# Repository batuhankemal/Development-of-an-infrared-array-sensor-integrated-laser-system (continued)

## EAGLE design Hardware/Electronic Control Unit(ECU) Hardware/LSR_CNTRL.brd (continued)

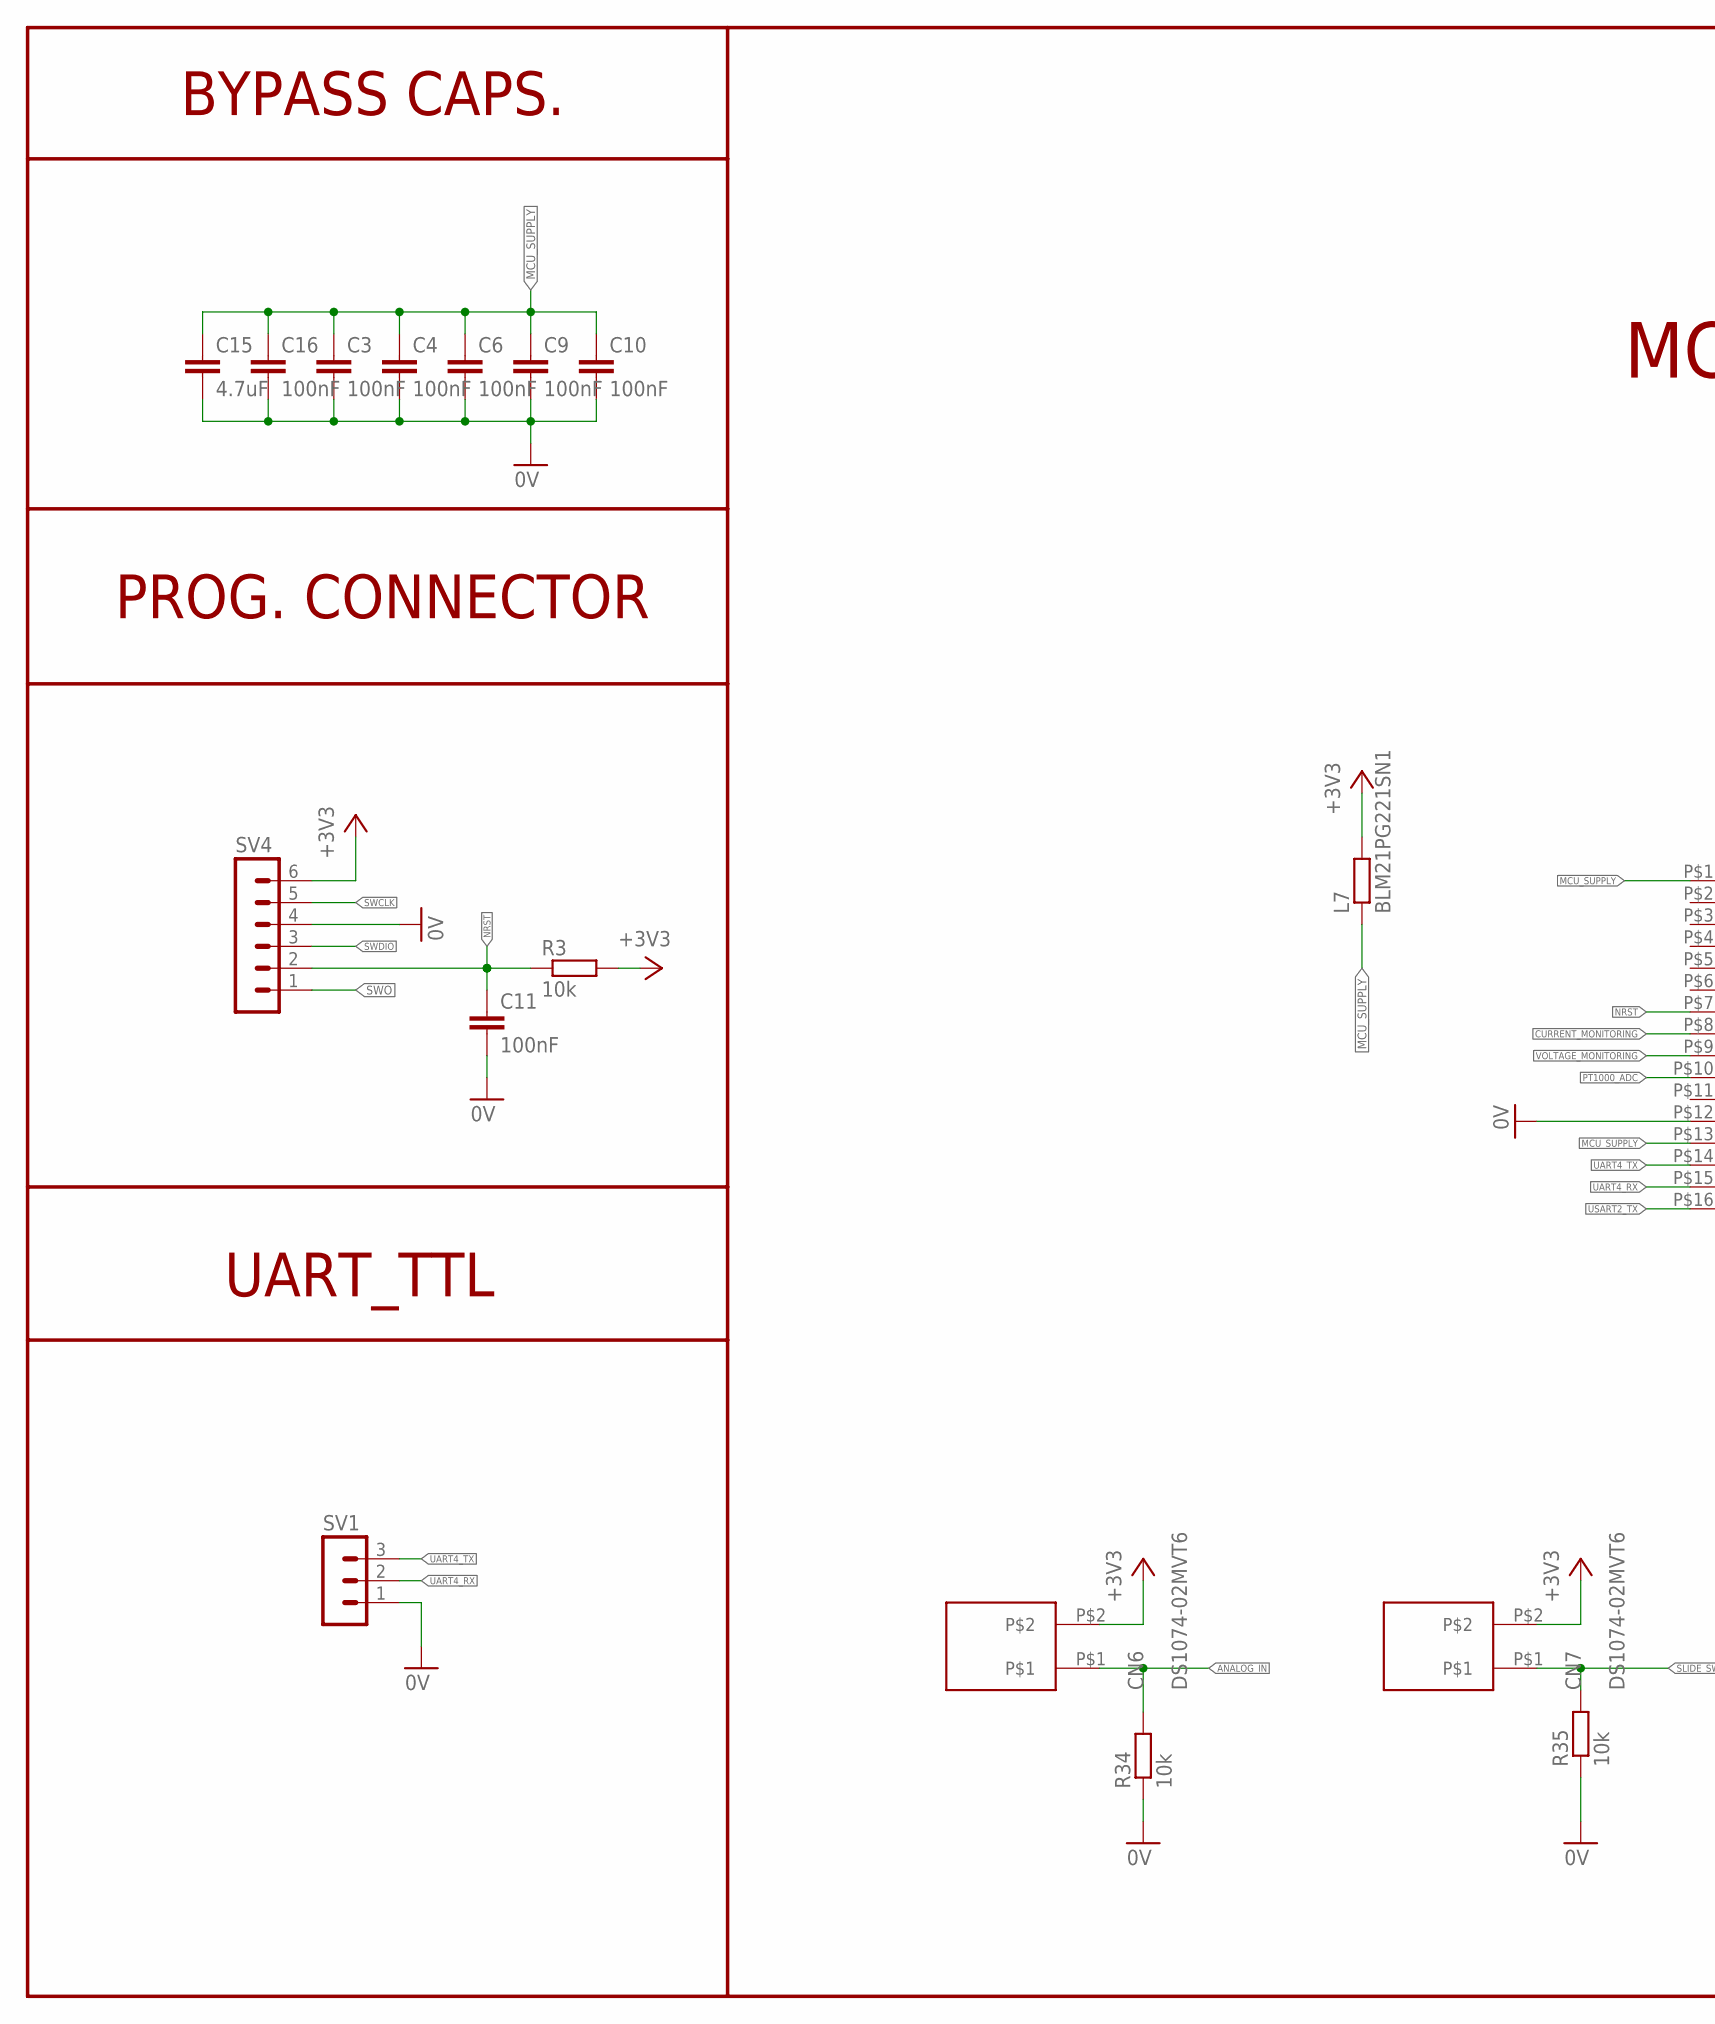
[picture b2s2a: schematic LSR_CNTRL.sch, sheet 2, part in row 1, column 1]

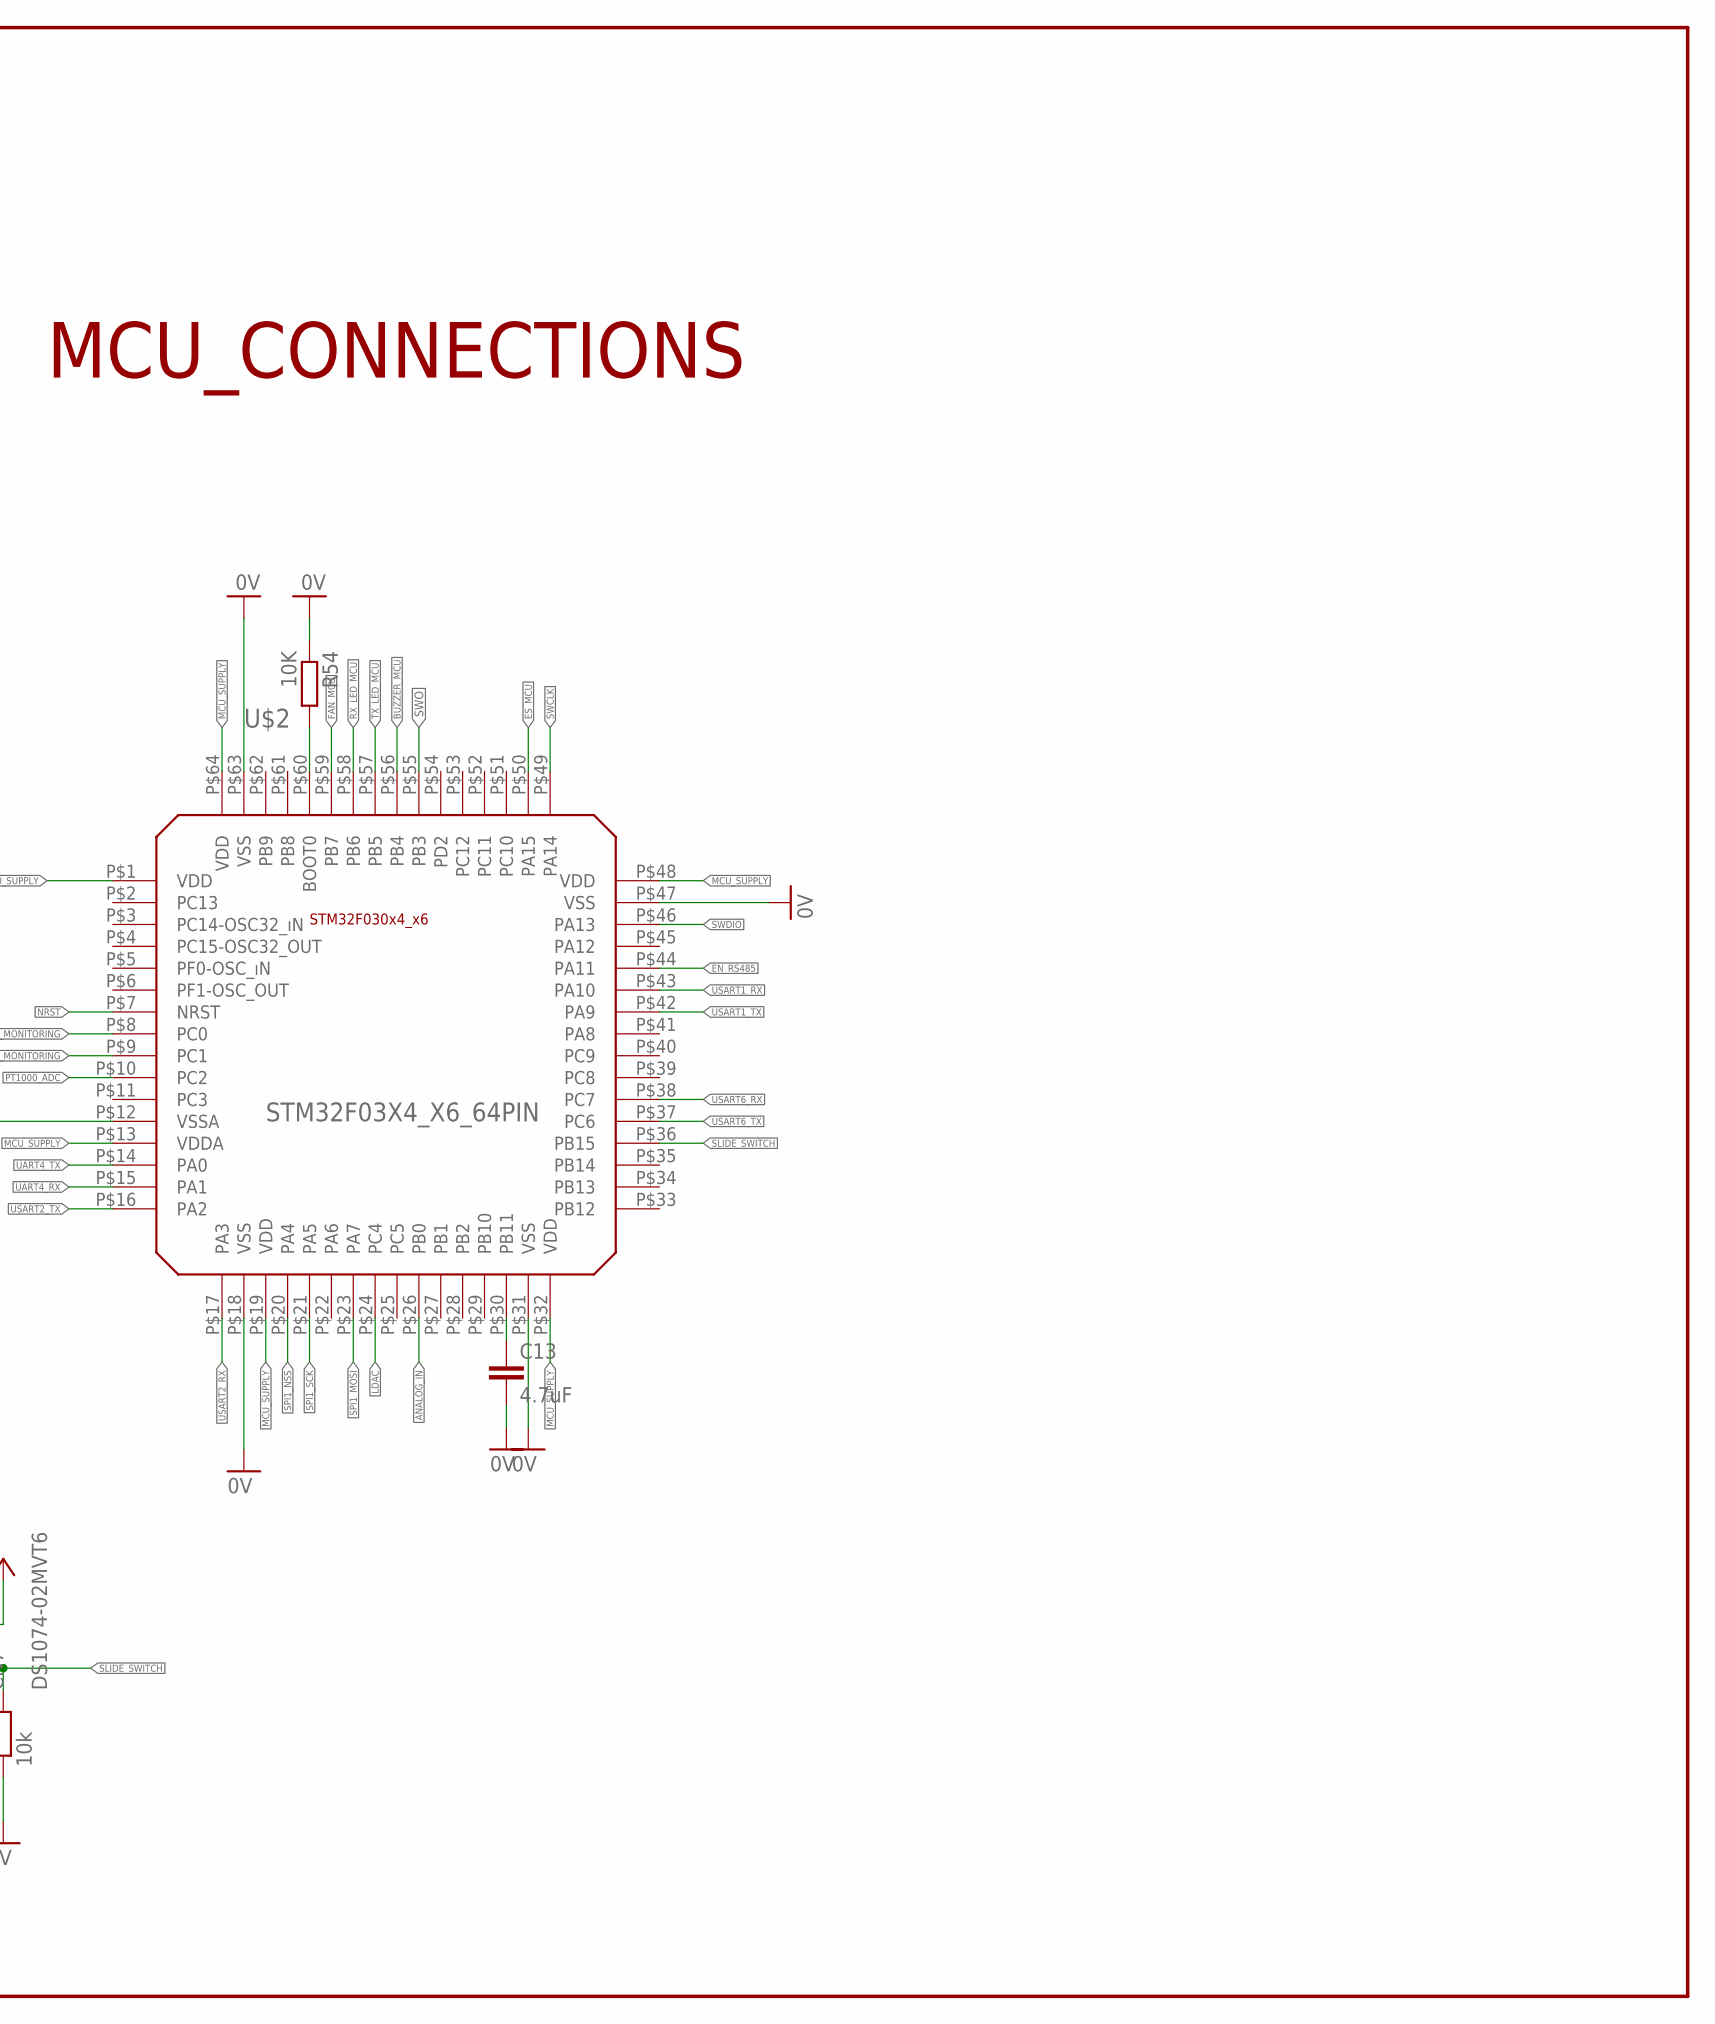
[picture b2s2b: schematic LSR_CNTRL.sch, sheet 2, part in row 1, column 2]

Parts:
C3, C4, C6, C9, C10, C11, C16: 100nF; C0603
C13, C15: 4.7uF; C0805
CN6, CN7: DS1074-02MVT6
L7: BLM21PG221SN1; R0805
R3, R34, R35: 10k; R0603
R54: 10K; R0603
SV1: MA03-1
SV4: MA06-1
U$2: STM32F03X4_X6_64PIN; LQFP64

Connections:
0V: C3.2, C4.2, C6.2, C9.2, C10.2, C11.2, C13.2, C15.2, C16.2, R34.1, R35.1, R54.1, SV1.1, SV4.4, U$2.P$12 (VSSA), U$2.P$18 (VSS), U$2.P$31 (VSS), U$2.P$47 (VSS), U$2.P$63 (VSS); also elsewhere on the board
+3V3: CN6.P$2, CN7.P$2, L7.2, R3.2, SV4.6; also elsewhere on the board
ANALOG_IN: CN6.P$1, R34.2, U$2.P$26 (PB0)
BUZZER_MCU: U$2.P$56 (PB4); also elsewhere on the board
CURRENT_MONITORING: U$2.P$8 (PC0); also elsewhere on the board
EN_RS485: U$2.P$44 (PA11); also elsewhere on the board
ES_MCU: U$2.P$50 (PA15); also elsewhere on the board
FAN_MCU: U$2.P$59 (PB7); also elsewhere on the board
LDAC: U$2.P$24 (PC4); also elsewhere on the board
MCU_SUPPLY: C3.1, C4.1, C6.1, C9.1, C10.1, C15.1, C16.1, L7.1, U$2.P$1 (VDD), U$2.P$13 (VDDA), U$2.P$19 (VDD), U$2.P$32 (VDD), U$2.P$48 (VDD), U$2.P$64 (VDD)
unnamed: C13.1, U$2.P$30 (PB11)
unnamed: R54.2, U$2.P$60 (BOOT0)
NRST: C11.1, R3.1, SV4.2, U$2.P$7 (NRST)
PT1000_ADC: U$2.P$10 (PC2); also elsewhere on the board
RX_LED_MCU: U$2.P$58 (PB6); also elsewhere on the board
SLIDE_SWITCH: CN7.P$1, R35.2, U$2.P$36 (PB15)
SPI1_MOSI: U$2.P$23 (PA7); also elsewhere on the board
SPI1_NSS: U$2.P$20 (PA4); also elsewhere on the board
SPI1_SCK: U$2.P$21 (PA5); also elsewhere on the board
SWCLK: SV4.5, U$2.P$49 (PA14)
SWDIO: SV4.3, U$2.P$46 (PA13)
SWO: SV4.1, U$2.P$55 (PB3)
TX_LED_MCU: U$2.P$57 (PB5); also elsewhere on the board
UART4_RX: SV1.2, U$2.P$15 (PA1)
UART4_TX: SV1.3, U$2.P$14 (PA0)
USART1_RX: U$2.P$43 (PA10); also elsewhere on the board
USART1_TX: U$2.P$42 (PA9); also elsewhere on the board
USART2_RX: U$2.P$17 (PA3); also elsewhere on the board
USART2_TX: U$2.P$16 (PA2); also elsewhere on the board
USART6_RX: U$2.P$38 (PC7); also elsewhere on the board
USART6_TX: U$2.P$37 (PC6); also elsewhere on the board
VOLTAGE_MONITORING: U$2.P$9 (PC1); also elsewhere on the board

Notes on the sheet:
BYPASS CAPS.
PROG. CONNECTOR
MCU_CONNECTIONS
UART_TTL

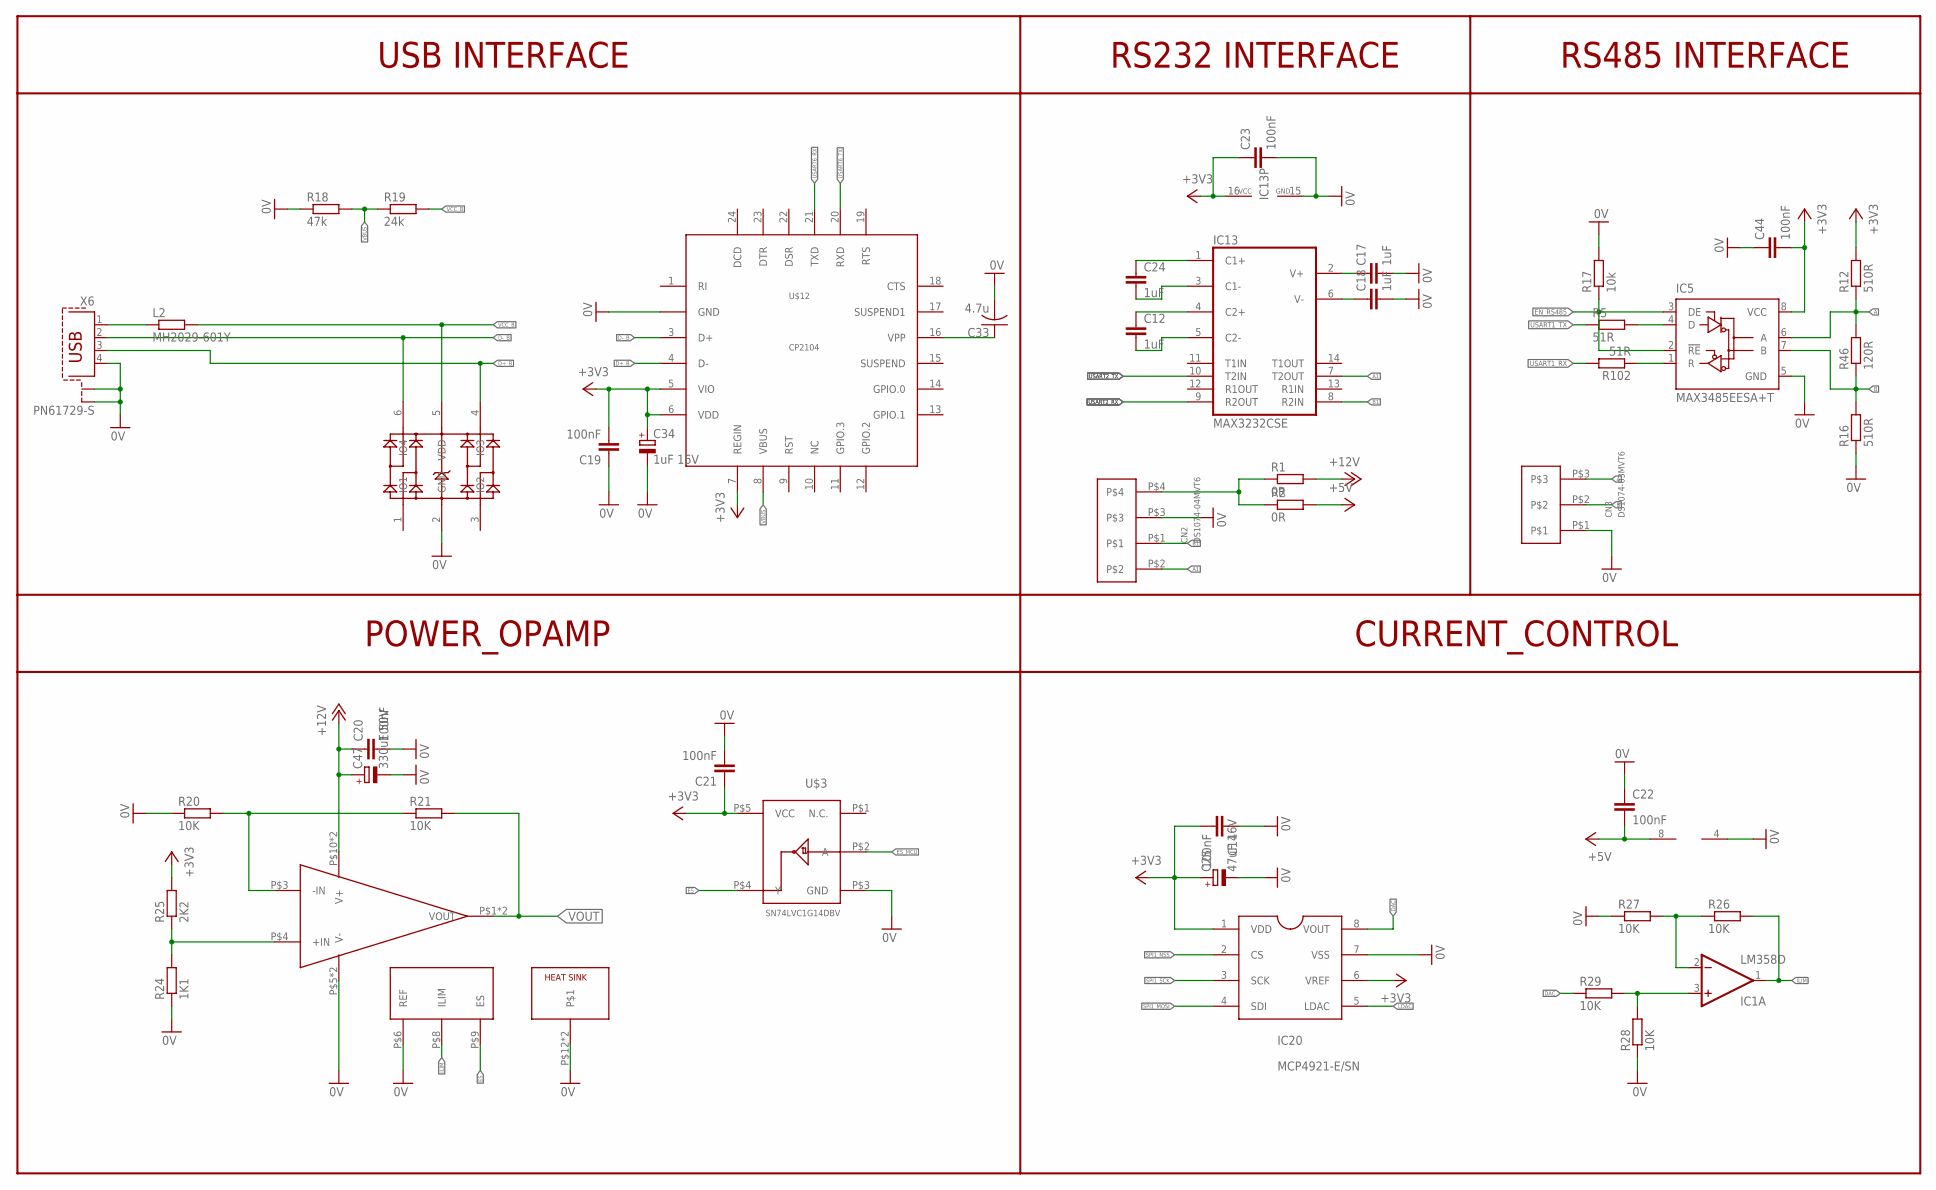
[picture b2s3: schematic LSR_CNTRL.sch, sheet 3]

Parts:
C12, C17, C18, C24: 1uF; C1206
C14, C19, C20, C21, C22, C23, C44: 100nF; C0603
C25: 47uF 16V; B/3528-21R
C33: 4.7u; C0805
C34: 1uF 16V; SMC_Z
C47: 330uF 50V; E5-10,5
CN2: DS1074-04MVT6
CN3: DS1074-03MVT6
IC1: LM358D; SO08
IC5: MAX3485EESA+T; D_R-PDSO-G8
IC13: MAX3232CSE; SO16
IC20: MCP4921-E/SN; SO-08-MCP
L2: MH2029-601Y; R0805
OPAMP1: OPA549MKVC
R1, R2: 0R; R0805
R5, R102: 51R; R0603
R12, R16: 510R; R0603
R17: 10k; R0603
R18: 47k; R0805
R19: 24k; R0805
R20, R21, R26, R27, R28, R29: 10K; R0805
R24: 1K1; R0805
R25: 2K2; R0805
R46: 120R; R0603
TVS1: 824001; SOT23-6
U$3: SN74LVC1G14DBV; SOT-23-DBV
U$12: CP2104
X6: PN61729-S

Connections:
0V: C14.1, C17.2, C18.2, C19.1, C20.2, C21.2, C22.1, C23.2, C25.-, C33.2, C34.-, C44.1, C47.-, CN2.P$3, CN3.P$1, IC1.4 (V-), IC5.5 (GND), IC13.15 (GND), IC20.7 (VSS), OPAMP1.P$5 (V-), OPAMP1.P$6 (REF), OPAMP1.P$7 (V-), OPAMP1.P$12, OPAMP1.P$13, R16.1, R17.2, R18.1, R20.1, R24.1, R27.1, R28.1, TVS1.2 (GND), U$3.P$3 (GND), U$12.2 (GND), U$12.GND1 (GND), X6.4, X6.S1, X6.S2; also elsewhere on the board
+3V3: C14.2, C19.2, C21.1, C23.1, C25.+, C34.+, C44.2, IC5.8 (VCC), IC13.16 (VCC), IC20.1 (VDD), IC20.6 (VREF), R12.2, R25.2, U$3.P$5 (VCC), U$12.5 (VIO), U$12.6 (VDD), U$12.7 (REGIN); also elsewhere on the board
+5V: C22.2, IC1.8 (V+), R2.2; also elsewhere on the board
+12V: C20.1, C47.+, OPAMP1.P$10 (V+), OPAMP1.P$11 (V+), R1.2; also elsewhere on the board
A: CN3.P$3, IC5.6 (A), R12.1, R46.2
A1: CN2.P$2, IC13.7 (T2OUT)
B: CN3.P$2, IC5.7 (B), R16.2, R46.1
B1: CN2.P$1, IC13.8 (R2IN)
D+_B: TVS1.4 (IO3), U$12.4 (D-), X6.3
D-_B: TVS1.6 (IO4), U$12.3 (D+), X6.2
DAC: IC20.8 (VOUT), R29.1
EN_RS485: IC5.2 (!RE), IC5.3 (DE), R17.1; also elsewhere on the board
ES: OPAMP1.P$9 (ES), U$3.P$4 (Y)
ES_MCU: U$3.P$2 (A); also elsewhere on the board
ILIM: IC1.1 (OUT), OPAMP1.P$8 (ILIM), R26.2
LDAC: IC20.5 (LDAC); also elsewhere on the board
unnamed: C18.1, IC13.6 (V-)
unnamed: OPAMP1.P$3 (-IN), R20.2, R21.1
unnamed: IC1.2 (-IN), R26.1, R27.2
unnamed: OPAMP1.P$4 (+IN), R24.2, R25.1
unnamed: IC1.3 (+IN), R28.2, R29.2
unnamed: IC5.4 (D), R5.2
unnamed: C33.1, U$12.16 (VPP)
unnamed: L2.1, X6.1
unnamed: C24.1, IC13.1 (C1+)
unnamed: C24.2, IC13.3 (C1-)
unnamed: IC5.1 (R), R102.1
unnamed: C12.1, IC13.4 (C2+)
unnamed: C12.2, IC13.5 (C2-)
unnamed: C17.1, IC13.2 (V+)
SPI1_MOSI: IC20.4 (SDI); also elsewhere on the board
SPI1_NSS: IC20.2 (CS); also elsewhere on the board
SPI1_SCK: IC20.3 (SCK); also elsewhere on the board
SUPPLY: CN2.P$4, R1.1, R2.1
USART1_RX: R102.2; also elsewhere on the board
USART1_TX: R5.1; also elsewhere on the board
USART2_RX: IC13.9 (R2OUT); also elsewhere on the board
USART2_TX: IC13.10 (T2IN); also elsewhere on the board
USART6_RX: U$12.21 (TXD); also elsewhere on the board
USART6_TX: U$12.20 (RXD); also elsewhere on the board
VBUS: R18.2, R19.1, U$12.8 (VBUS)
VCC_B: L2.2, R19.2, TVS1.5 (VDD)
VOUT: OPAMP1.P$1 (VOUT), OPAMP1.P$2 (VOUT), R21.2; also elsewhere on the board

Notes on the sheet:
USB INTERFACE
RS232 INTERFACE
RS485 INTERFACE
CURRENT_CONTROL
POWER_OPAMP

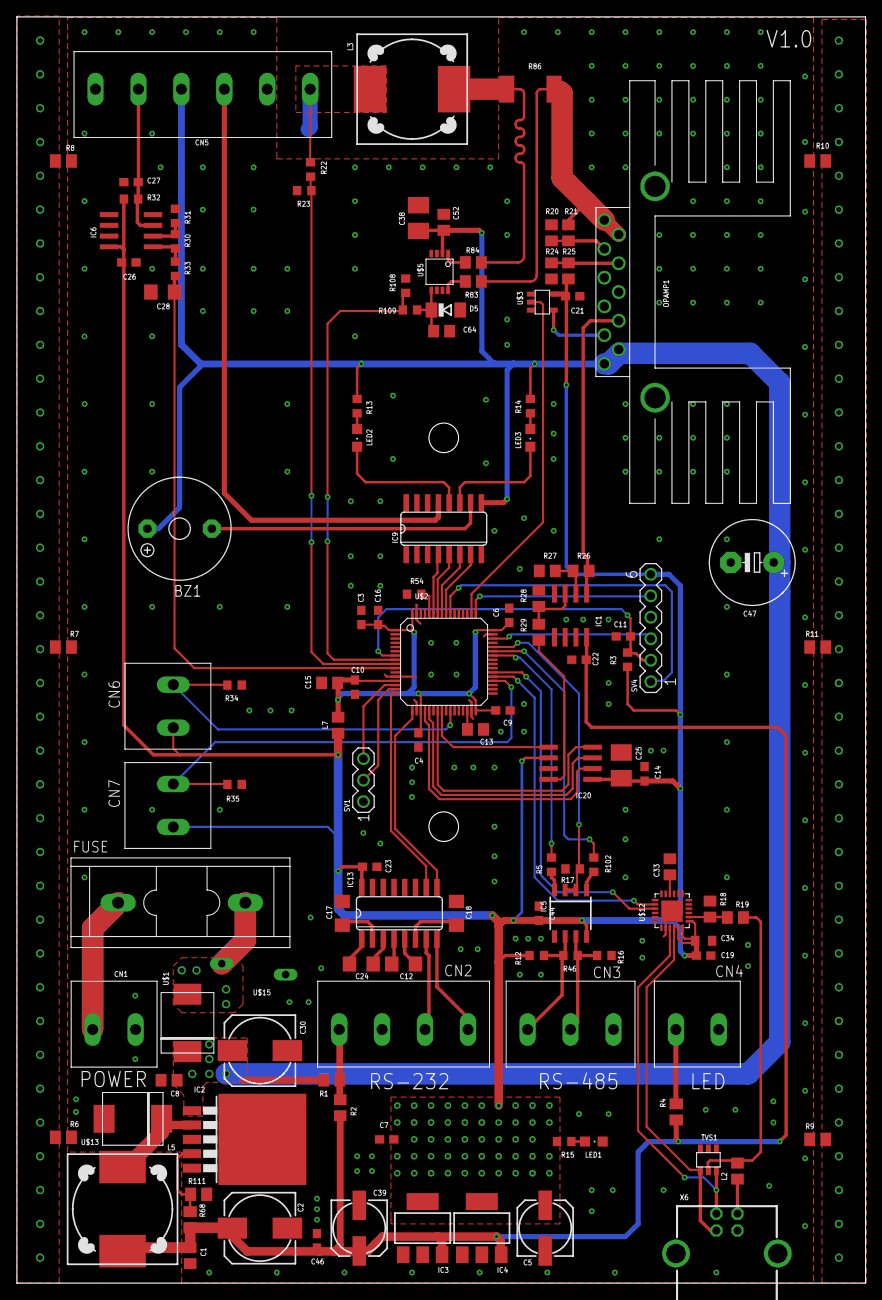
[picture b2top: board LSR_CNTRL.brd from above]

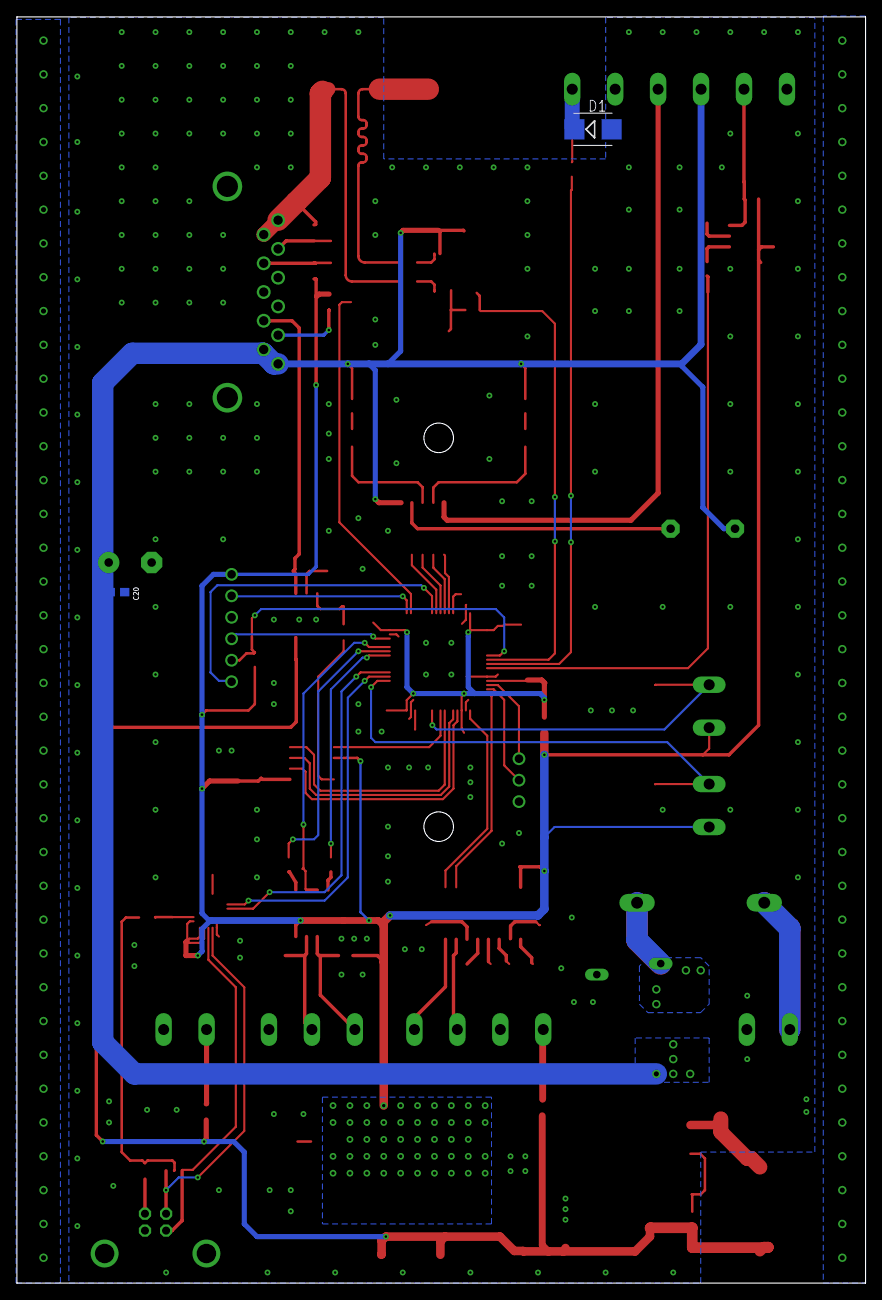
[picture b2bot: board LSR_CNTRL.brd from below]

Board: 2 copper layers, 100.4 x 149.8 mm, 122 parts (2 on the bottom side), 83 nets.

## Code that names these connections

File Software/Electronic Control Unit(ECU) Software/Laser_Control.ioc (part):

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Mcu.Name=STM32F446R(C-E)Tx
Mcu.Package=LQFP64
Mcu.UserName=STM32F446RCTx
PA10.Mode=Asynchronous
PA10.Signal=USART1_RX
PA11.GPIOParameters=GPIO_Label
PA11.GPIO_Label=RS_EN
PA11.Signal=GPIO_Output
PA13.Mode=Serial_Wire
PA13.Signal=SYS_JTMS-SWDIO
PA14.Mode=Serial_Wire
PA14.Signal=SYS_JTCK-SWCLK
PA15.GPIOParameters=GPIO_Label
PA15.GPIO_Label=ES_MCU
PA15.Signal=GPIO_Output
PA2.Mode=Asynchronous
PA2.Signal=USART2_TX
PA3.Mode=Asynchronous
PA3.Signal=USART2_RX
PA4.GPIOParameters=GPIO_Label
PA4.GPIO_Label=SPI_CS
PA4.Signal=GPIO_Output
PA5.Mode=TX_Only_Simplex_Unidirect_Master
PA5.Signal=SPI1_SCK
PA7.Mode=TX_Only_Simplex_Unidirect_Master
PA7.Signal=SPI1_MOSI
PA9.Mode=Asynchronous
PA9.Signal=USART1_TX
PB0.GPIOParameters=GPIO_Label
PB0.GPIO_Label=DEV_IN
PB0.Signal=GPIO_Input
PB15.GPIOParameters=GPIO_Label
PB15.GPIO_Label=SLIDE_SW
PB15.Signal=GPIO_Input
PB4.GPIOParameters=GPIO_Label
PB4.GPIO_Label=BUZZER
PB4.Signal=GPIO_Output
PB5.GPIOParameters=GPIO_Label
PB5.GPIO_Label=RX_LED
PB5.Signal=GPIO_Output
PB6.GPIOParameters=GPIO_Label
PB6.GPIO_Label=TX_LED
PB6.Signal=GPIO_Output
PB7.GPIOParameters=GPIO_Label
PB7.GPIO_Label=FAN
PB7.Signal=GPIO_Output
PC0.Signal=ADCx_IN10
PC1.Signal=ADCx_IN11
PC2.Signal=ADCx_IN12
PC4.GPIOParameters=GPIO_Label
PC4.GPIO_Label=LDAC
PC4.Signal=GPIO_Output
PC6.Mode=Asynchronous
PC6.Signal=USART6_TX
PC7.Mode=Asynchronous
PC7.Signal=USART6_RX
RCC.SYSCLKFreq_VALUE=180000000
RCC.SYSCLKSource=RCC_SYSCLKSOURCE_PLLCLK
board=custom

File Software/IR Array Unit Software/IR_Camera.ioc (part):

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Mcu.Name=STM32F446R(C-E)Tx
Mcu.Package=LQFP64
Mcu.UserName=STM32F446RCTx
PA0-WKUP.Mode=Asynchronous
PA0-WKUP.Signal=UART4_TX
PA1.Mode=Asynchronous
PA1.Signal=UART4_RX
PA10.Mode=Asynchronous
PA10.Signal=USART1_RX
PA11.GPIOParameters=GPIO_Label
PA11.GPIO_Label=RS_EN
PA11.Signal=GPIO_Output
PA13.Mode=Serial_Wire
PA13.Signal=SYS_JTMS-SWDIO
PA14.Mode=Serial_Wire
PA14.Signal=SYS_JTCK-SWCLK
PA2.Mode=Asynchronous
PA2.Signal=USART2_TX
PA3.Mode=Asynchronous
PA3.Signal=USART2_RX
PA4.GPIOParameters=GPIO_Label
PA4.GPIO_Label=SPI_CS
PA4.Signal=GPIO_Output
PA9.Mode=Asynchronous
PA9.Signal=USART1_TX
PB6.GPIOParameters=GPIO_Pu
PB6.GPIO_Pu=GPIO_PULLUP
PB6.Mode=I2C
PB6.Signal=I2C1_SCL
PB7.GPIOParameters=GPIO_Pu
PB7.GPIO_Pu=GPIO_PULLUP
PB7.Mode=I2C
PB7.Signal=I2C1_SDA
PC10.GPIOParameters=GPIO_Label
PC10.GPIO_Label=LASER_P1
PC10.Signal=GPIO_Output
PC11.GPIOParameters=GPIO_Label
PC11.GPIO_Label=RX_LED
PC11.Signal=GPIO_Output
PC12.GPIOParameters=GPIO_Label
PC12.GPIO_Label=TX_LED
PC12.Signal=GPIO_Output
PD2.GPIOParameters=GPIO_Label
PD2.GPIO_Label=LASER_P2
PD2.Signal=GPIO_Output
RCC.SYSCLKFreq_VALUE=180000000
RCC.SYSCLKSource=RCC_SYSCLKSOURCE_PLLCLK
board=custom

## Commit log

2024-10-23 First Commit on Github
    23.10.2024
